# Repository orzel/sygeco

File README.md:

Small console based on attiny85, compatible with tinyjoypad.

The official homepage is https://projects.freehackers.org/sygeco1/
and the mercurial repository is at https://freehackers.org/electronics/sygeco1/

It is developed by [Thomas Capricelli](https://freehackers.org/thomas/).

The `hardware/` directory contains kicad files for the schematics and pcb, as well as some support files for parts and 3d rendering.
The `launcher/` directory provides a PyQt script to easily select and program ("upload") any game. It's easily customizable, if you want to add/change games or configure the `avrdude` programmer used.

No games is included in the repository, though. The project page has a zip file with the launcher and most available games, pre-configured.

I can be contacted [on this page](https://www.freehackers.org/thomas/feedback/).

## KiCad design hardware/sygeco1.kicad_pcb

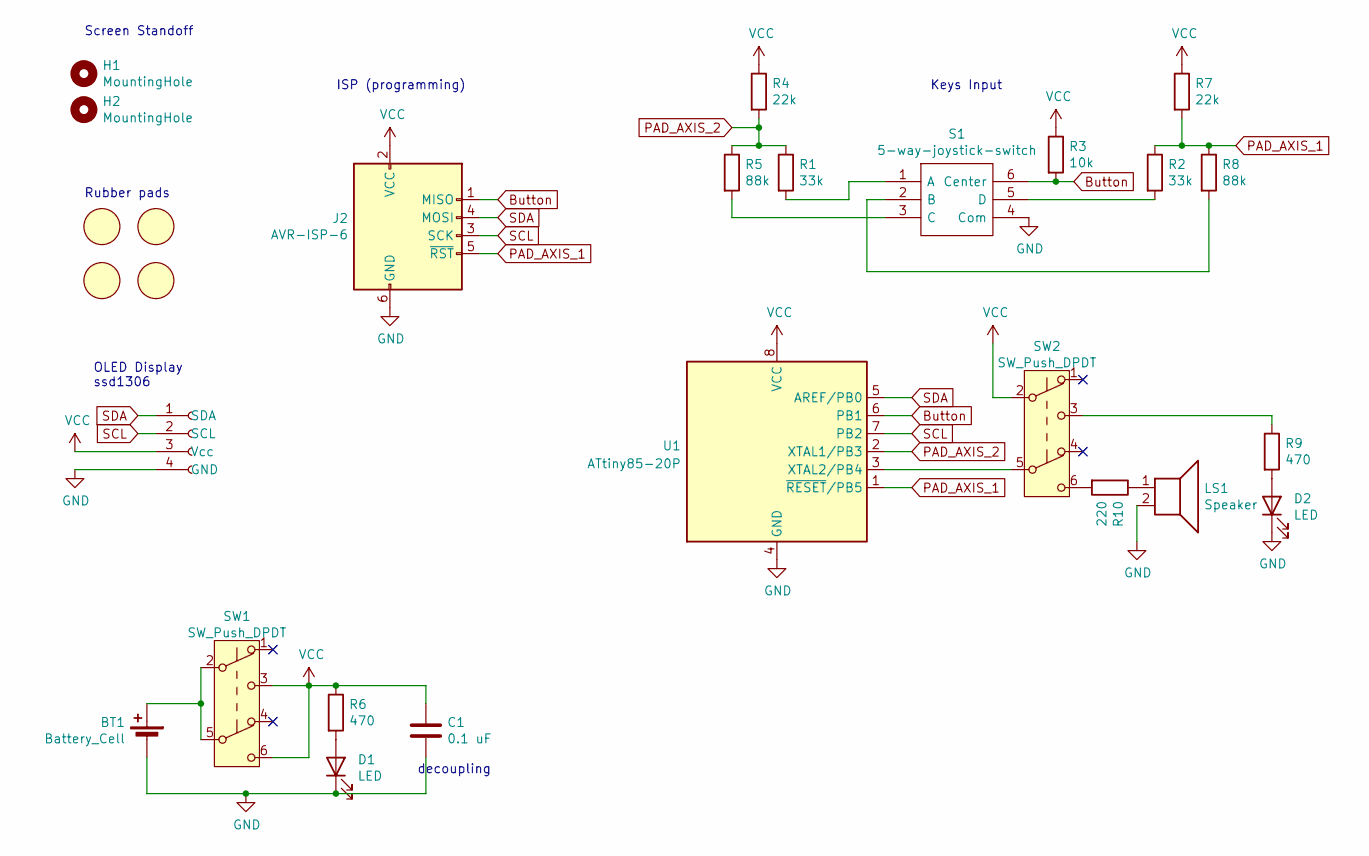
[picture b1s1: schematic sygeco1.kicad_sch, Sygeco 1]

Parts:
BT1: Battery_Cell; BatteryHolder_China_1x20mm
C1: 0.1 uF; C_1206_3216Metric_Pad1.33x1.80mm_HandSolder
D1, D2: LED; LED_1206_3216Metric
H1, H2: MountingHole; MountingHole_2.2mm_M2_ISO7380_Pad
J1: SSD1306_module; PinSocket_1x04_P2.54mm_Vertical
J2: AVR-ISP-6; PinHeader_2x03_P2.54mm_Vertical
LS1: Speaker; MagneticBuzzer_ProSignal_ABT-410-RC
R1, R2: 33k; R_1206_3216Metric_Pad1.30x1.75mm_HandSolder
R3: 10k; R_1206_3216Metric_Pad1.30x1.75mm_HandSolder
R4, R7: 22k; R_1206_3216Metric_Pad1.30x1.75mm_HandSolder
R5, R8: 88k; R_1206_3216Metric_Pad1.30x1.75mm_HandSolder
R6, R9: 470; R_1206_3216Metric_Pad1.30x1.75mm_HandSolder
R10: 220; R_1206_3216Metric_Pad1.30x1.75mm_HandSolder
RP1, RP2, RP3, RP4: silicone_rubber_pad
S1: 5-way-joystick-switch; SKQUCAA010; Manufacturer_Part_Number SKQUCAA010; Mouser Part Number 688-SKQUCA
SW1, SW2: SW_Push_DPDT; DPDT_Switch_with_lock
U1: ATtiny85-20P; DIP-8_W7.62mm

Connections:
Button: J2.1 (MISO), R3.2, S1.6 (Center), U1.6 (PB1)
GND: BT1.2 (-), C1.2, D1.1 (K), D2.1 (K), J1.4 (GND), J2.6 (GND), LS1.2, S1.4 (Com), U1.4 (GND)
unnamed: BT1.1 (+), SW1.2 (B), SW1.5 (B)
unnamed: D1.2 (A), R6.2
unnamed: D2.2 (A), R9.2
unnamed: LS1.1, R10.1
unnamed: R1.2, S1.1 (A)
unnamed: R2.2, S1.5 (D)
unnamed: R5.2, S1.3 (C)
unnamed: R8.2, S1.2 (B)
unnamed: R9.1, SW2.3 (C)
unnamed: R10.2, SW2.6 (C)
unnamed: SW2.5 (B), U1.3 (XTAL2/PB4)
PAD_AXIS_1: J2.5 (~RST), R2.1, R7.2, R8.1, U1.1 (~RESET/PB5)
PAD_AXIS_2: R1.1, R4.2, R5.1, U1.2 (XTAL1/PB3)
SCL: J1.2 (SCL), J2.3 (SCK), U1.7 (PB2)
SDA: J1.1 (SDA), J2.4 (MOSI), U1.5 (AREF/PB0)
VCC: C1.1, J1.3 (Vcc), J2.2 (VCC), R3.1, R4.1, R6.1, R7.1, SW1.3 (C), SW1.6 (C), SW2.2 (B), U1.8 (VCC)

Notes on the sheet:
Screen Standoff
decoupling
Rubber pads
OLED Display ssd1306
Keys Input
ISP (programming)

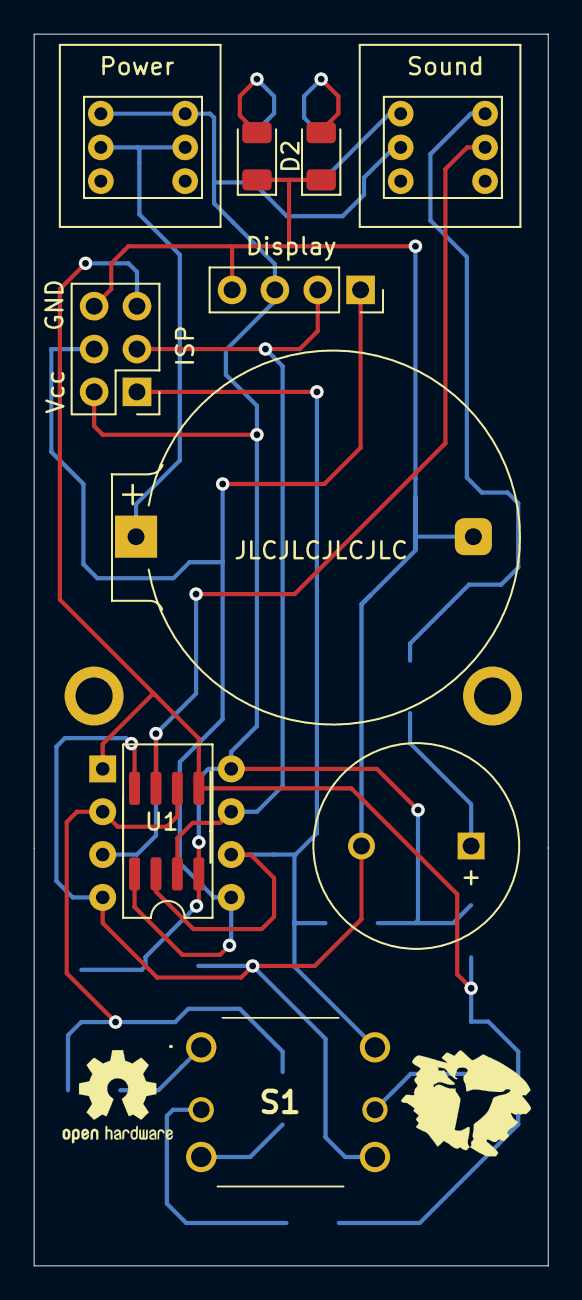
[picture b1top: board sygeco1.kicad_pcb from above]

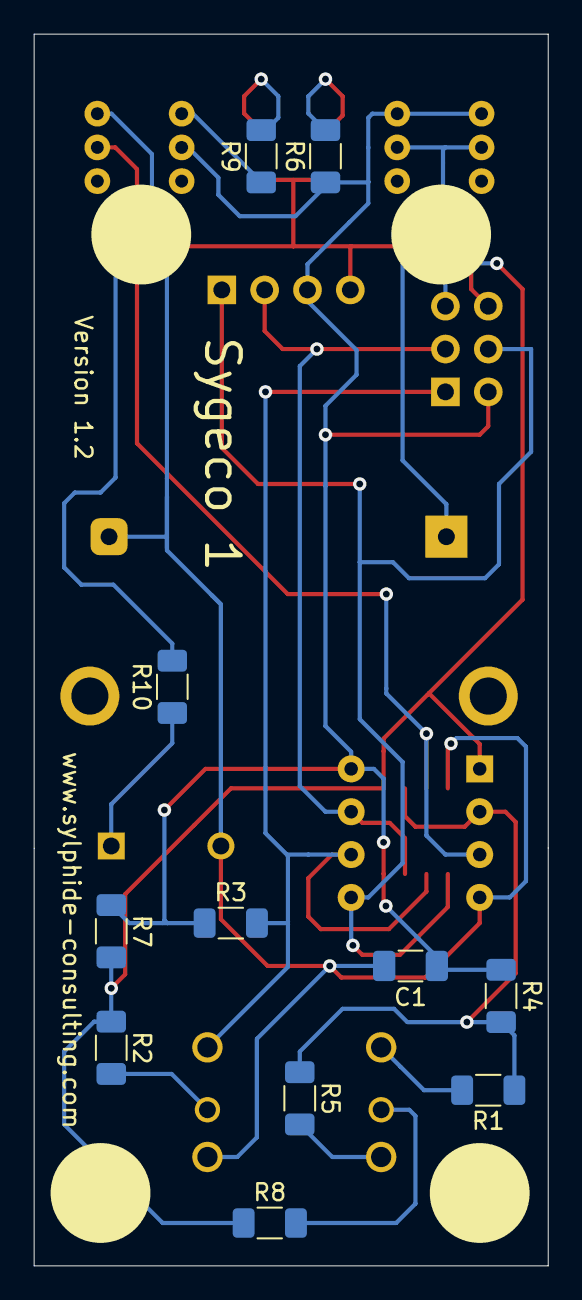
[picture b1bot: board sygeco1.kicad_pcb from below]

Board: 2 copper layers, 30.5 x 73.0 mm, 27 parts (15 on the bottom side), 18 nets.

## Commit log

2020-11-04 initial .hgignore
2020-11-04 blank new kicad project
2020-11-06 Done schematic + pcb routing
2020-11-06 hard to understand the purpose of all kicad file types..
2020-11-06 add some text/logo
2020-11-07 keep on 'improving'. Changed beeper and cell battery holder, according to what i can get my hand on.
2020-11-07 add an ISP header, a power led, and redo completely the routing: * the board is bigger, but hopefully more 'practical' to use * using two layers of copper. it's the same price, why bother ?
2020-11-07 commit gerber/drill files ("output")
2020-11-07 add decoupling capacitor, use same value for keypad resistors, it's simpler
2020-11-07 cleaning
2020-11-08 hopefully not used very often
2020-11-08 this file seems important..
2020-11-08 oops, the oled connector position was inversed, fixed that
2020-11-12 not sure how important this is
2020-11-12 cleaning / small improvements
2020-11-12 update gerbers, we use both Cu planes now
2020-11-12 start working on the BOM
2020-11-12 pcb makers want a zip
2020-11-18 copy all games from https://www.tinyjoypad.com/tinyjoypad_attiny85 * remove schematics * remove screenshots * remove hex * moved COPYING.txt one level up. md5s for all COPYING.txt were exactly the sa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
2020-11-18 clean unbearable indentation mess and other messy stuff (using astyle)
2020-11-18 rename *.ino to please arduino IDE
2020-11-18 forgot this one
2020-11-18 forgot this one too, i wonder how ..
2020-11-18 astyle it
2020-12-03 sync with my generic hgignore
2020-12-03 few fixes * sch: fix typo (axe -> axis) * reduce battery holder hole size now that i have the actual device to check * some routing cleaning * contrary to my expectation, the isp header works as is, 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
2020-12-13 Introduce the 'launcher', a small Qt/PySide2 script to choose a game and upload it. You can configure: * games (need a hex file and an image for each) * avrdude intalled in the path * the avrdude pro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
2020-12-13 add mounting holes for the screen
2020-12-13 Restore original (tinyjoypad) input schematics, with dual resistors and reset pin >= vcc/2
2020-12-13 Add a led to provide feedback about whether the sound is enable or not.
2020-12-13 make it executable under unix
2020-12-13 Add a resistor to lower the level of buzzer (especially when using li-ion battery, with higher voltage) + fixes leds resistors.
2020-12-14 Added tag pcb-production-0.1 for changeset 0c22d51a9606
2020-12-14 final touch + generates files for pcb production
2020-12-14 not sure what kicad changed here..
2020-12-14 update bom
2021-01-08 Make battery holders via holes slightly bigger. They fit as is, but it was tight.
2021-01-08 Added tag pcb-production-0.2 for changeset a1f5023423d9
2021-02-18 not needed anymore
2021-02-18 Too specific
2021-02-18 tweaking (now that we have more games)
2021-02-18 update all generated files before release
2021-02-18 update revision (1.0)
2021-02-22 add basic README
2021-02-23 I dont want to commit binaries. I provide a full-blown complete zip with all games on the hackaday page anyway.
2021-02-23 Implement translations (or i18n if you prefer). Switch to English as main language, and French is now the only translation. Feel free to send me any other if you wish.
2021-02-24 Added tag version-0.1 for changeset d486fd0df2e7
2021-12-12 add photos to the main git page
2021-12-12 migrated files to kicad 6.0 (-rc1)
2022-01-31 French translation: fix two typos
2022-11-20 random cleaning, mostly kicad updating its stuff
2022-11-20 some more
2022-11-20 add 3d model for DPDT switches
2022-11-20 not meant to be in source control
2022-11-20 use https://github.com/github/gitignore/blob/main/KiCad.gitignore for kicad files
2022-11-20 "migrate" our local symbols lib.
2022-11-20 Create new symbol+footprint for basic rubber pads.
2022-11-20 fix version number..
2022-11-24 Add some (silicone) pads. pcb: cleaning all errors/warnings
2022-11-24 Better align pads
2022-11-24 Fix attiny85 symbol + all errors/warnings. Seems like my symbol was obsolate..(?)
2022-11-25 fix name of lib
2022-11-25 slight offset on batteryholder 3d model
2022-11-25 make it more general
2022-11-25 Add dual footprints for the MCU. This way you can put either a dip8 or a sop8. Quite useful in those times of parts shortage.
2023-02-21 output files for 1.1
2023-02-22 Added tag version-1.1 for changeset 88719b0f9183
2023-04-10 doc++
2024-06-16 no more with recent kicad
2024-06-16 switching to kicad 8
2025-02-13 brings description from hackaday to our local mkdocs
2025-02-13 mkdocs: add downloads
2025-02-13 fix missing author
2025-02-25 new homepage
2025-02-25 oops
2025-03-15 Pyside has change it's naming scheme, adapt to it.
2025-03-15 doc: fix typo
2025-03-22 our own footer
2025-03-22 update symbols + revision
2025-03-22 dunno.. probably changes induced by a more recent version of kicad
2025-03-22 was referencing the old 'sygeco' local symbol library, fixed that to sygeco1
2025-03-22 kicad doing its stuff.. ?
2025-03-22 updated from schematics
2025-03-22 update schematic revision as well
2025-03-22 Add generated page, by the superb 'interactive html bom' plugin.
2025-03-22 the real name is 'sygeco 1'
2025-03-22 Move ibom to mkdocs directory + link from main file, don't use compression (that's bad for source control).
2025-03-22 add an interactive page witht the pcb in 3d requires proper js files on server.
2025-03-23 wikipedia seems to say KiCad is the proper spelling
2025-03-23 proofreading
2025-03-23 update version as displayed on pcb yeah, kicad has something about 'variables' i could surely use here
2025-03-23 We now provide a downloadble zip, no need to keep those generated files in source control anymore.
2025-03-23 update zip files
2025-03-24 It behaves weirdly when rotating, which was not the case in my previous testing..
2025-03-24 fix link
2025-03-25 text++
2025-03-25 update vrml file
